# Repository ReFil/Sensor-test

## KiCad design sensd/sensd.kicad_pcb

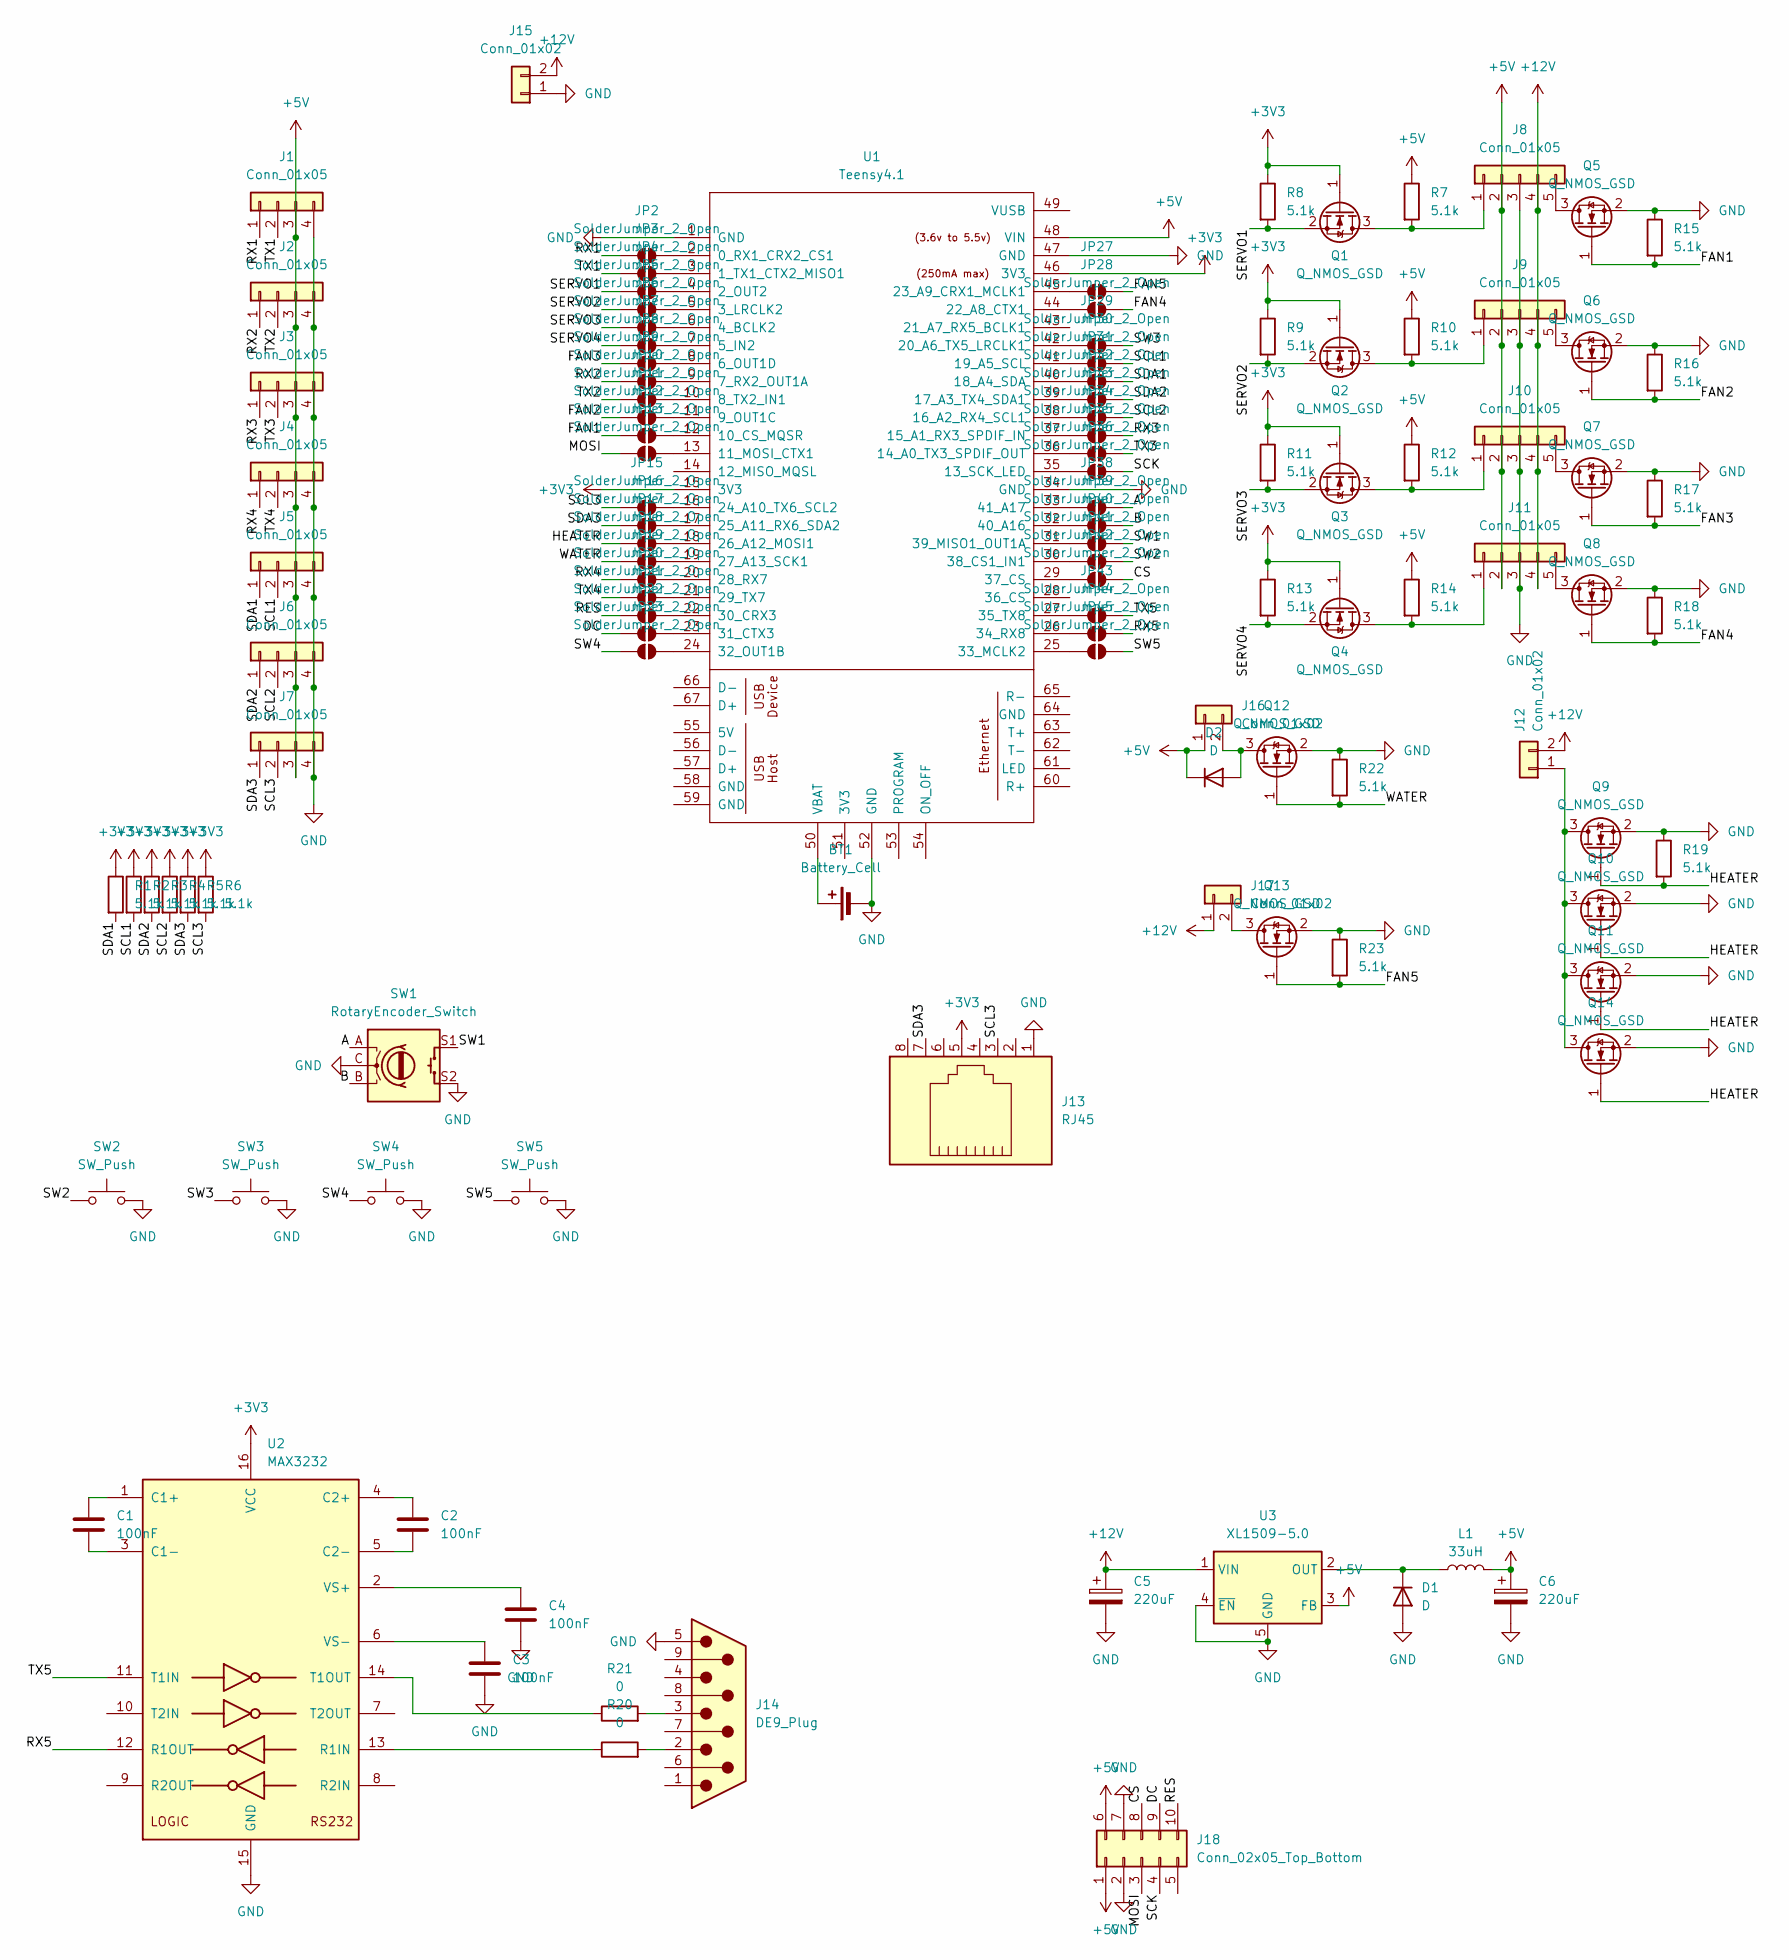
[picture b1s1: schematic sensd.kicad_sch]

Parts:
BT1: Battery_Cell; BatteryHolder_ComfortableElectronic_CH273-2450_1x2450
C1, C2, C3, C4: 100nF; C_0603_1608Metric; LCSC Part C1591
C5, C6: 220uF; CP_Elec_6.3x7.7; LCSC Part C2827940
D1, D2: D; D_SMA; LCSC Part C85098
J1, J2, J3, J4, J5, J6, J7: Conn_01x05; PinSocket_1x04_P2.54mm_Vertical
J8, J9, J10, J11: Conn_01x05; PinSocket_1x05_P2.54mm_Vertical
J12: Conn_01x02; AMASS_XT30PW-F_1x02_P2.50mm_Horizontal
J13: RJ45; RJ45_Amphenol_54602-x08_Horizontal
J14: DE9_Plug; DSUB-9_Female_Vertical_P2.77x2.84mm
J15: Conn_01x02; AMASS_XT60PW-M_1x02_P7.20mm_Horizontal
J16, J17: Conn_01x02; PinSocket_1x02_P2.54mm_Vertical
J18: Conn_02x05_Top_Bottom; PinHeader_2x05_P2.54mm_Vertical
JP2, JP3, JP4, JP5, JP6, JP7, JP8, JP9, JP10, JP11, JP12, JP13, JP15, JP16, JP17, JP18, JP19, JP20, JP21, JP22, JP23, JP27, JP28, JP29, JP30, JP31, JP32, JP33, JP34, JP35, JP36, JP38, JP39, JP40, JP41, JP42, JP43, JP44, JP45: SolderJumper_2_Open; SolderJumper-2_P1.3mm_Open_TrianglePad1.0x1.5mm
L1: 33uH; L_7.3x7.3_H3.5; LCSC Part C3002653
Q1, Q2, Q3, Q4, Q5, Q6, Q7, Q8, Q9, Q10, Q11, Q12, Q13, Q14: Q_NMOS_GSD; SOT-23; LCSC Part C414015
R1, R2, R3, R4, R5, R6, R7, R8, R9, R10, R11, R12, R13, R14, R15, R16, R17, R18, R19, R22, R23: 5.1k; R_0603_1608Metric; LCSC Part C26000
R20, R21: 0; R_0603_1608Metric
SW1: RotaryEncoder_Switch; RotaryEncoder_Bourns_Vertical_PEC12R-3x17F-Sxxxx
SW2, SW3, SW4, SW5: SW_Push; SW_Cherry_MX_1.00u_PCB
U1: Teensy4.1; Teensy41
U2: MAX3232; SOIC-16_3.9x9.9mm_P1.27mm; LCSC Part C45843
U3: XL1509-5.0; SOIC-8_3.9x4.9mm_P1.27mm; LCSC Part C2902368

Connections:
+3V3: J13.5, Q1.1 (G), Q2.1 (G), Q3.1 (G), Q4.1 (G), R1.1, R2.1, R3.1, R4.1, R5.1, R6.1, R8.1, R9.1, R11.1, R13.1, U1.15 (3V3), U1.46 (3V3), U2.16 (VCC)
+5V: C6.1, D2.1 (K), J1.3, J2.3, J3.3, J4.3, J5.3, J6.3, J7.3, J8.2, J9.2, J10.2, J11.2, J16.1, J18.1, J18.6, L1.2, R7.1, R10.1, R12.1, R14.1, U1.48 (VIN), U3.3 (FB)
+12V: C5.1, J8.4, J9.4, J10.4, J11.4, J12.2, J15.2, J17.1, U3.1 (VIN)
/A: JP38.2 (B), SW1.A
/B: JP39.2 (B), SW1.B
/CS: J18.8, JP42.2 (B)
/DC: J18.9, JP22.1 (A)
/FAN1: JP12.1 (A), Q5.1 (G), R15.2
/FAN2: JP11.1 (A), Q6.1 (G), R16.2
/FAN3: JP8.1 (A), Q7.1 (G), R17.2
/FAN4: JP28.2 (B), Q8.1 (G), R18.2
/FAN5: JP27.2 (B), Q13.1 (G), R23.2
/HEATER: JP17.1 (A), Q9.1 (G), Q10.1 (G), Q11.1 (G), Q14.1 (G), R19.2
/MOSI: J18.3, JP13.1 (A)
/RES: J18.10, JP21.1 (A)
/RX1: J1.1, JP2.1 (A)
/RX2: J2.1, JP9.1 (A)
/RX3: J3.1, JP34.2 (B)
/RX4: J4.1, JP19.1 (A)
/RX5: JP44.2 (B), U2.12 (R1OUT)
/SCK: J18.4, JP36.2 (B)
/SCL1: J5.2, JP30.2 (B), R2.2
/SCL2: J6.2, JP33.2 (B), R4.2
/SCL3: J7.2, J13.3, JP15.1 (A), R6.2
/SDA1: J5.1, JP31.2 (B), R1.2
/SDA2: J6.1, JP32.2 (B), R3.2
/SDA3: J7.1, J13.7, JP16.1 (A), R5.2
/SERVO1: JP4.1 (A), Q1.2 (S), R8.2
/SERVO2: JP5.1 (A), Q2.2 (S), R9.2
/SERVO3: JP6.1 (A), Q3.2 (S), R11.2
/SERVO4: JP7.1 (A), Q4.2 (S), R13.2
/SW1: JP40.2 (B), SW1.S1
/SW2: JP41.2 (B), SW2.1
/SW3: JP29.2 (B), SW3.1
/SW4: JP23.1 (A), SW4.1
/SW5: JP45.2 (B), SW5.1
/TX1: J1.2, JP3.1 (A)
/TX2: J2.2, JP10.1 (A)
/TX3: J3.2, JP35.2 (B)
/TX4: J4.2, JP20.1 (A)
/TX5: JP43.2 (B), U2.11 (T1IN)
/WATER: JP18.1 (A), Q12.1 (G), R22.2
GND: BT1.2 (-), C3.2, C4.2, C5.2, C6.2, D1.2 (A), J1.4, J2.4, J3.4, J4.4, J5.4, J6.4, J7.4, J8.3, J9.3, J10.3, J11.3, J13.1, J14.5, J15.1, J18.2, J18.7, Q5.2 (S), Q6.2 (S), Q7.2 (S), Q8.2 (S), Q9.2 (S), Q10.2 (S), Q11.2 (S), Q12.2 (S), Q13.2 (S), Q14.2 (S), R15.1, R16.1, R17.1, R18.1, R19.1, R22.1, R23.1, SW1.C, SW1.S2, SW2.2, SW3.2, SW4.2, SW5.2, U1.1 (GND), U1.34 (GND), U1.47 (GND), U1.52 (GND), U2.15 (GND), U3.4 (~EN), U3.5 (GND), U3.6 (GND), U3.7 (GND), U3.8 (GND)
unnamed: BT1.1 (+), U1.50 (VBAT)
unnamed: D1.1 (K), L1.1, U3.2 (OUT)
unnamed: D2.2 (A), J16.2, Q12.3 (D)
unnamed: J8.1, Q1.3 (D), R7.2
unnamed: J8.5, Q5.3 (D)
unnamed: J9.1, Q2.3 (D), R10.2
unnamed: J9.5, Q6.3 (D)
unnamed: J10.1, Q3.3 (D), R12.2
unnamed: J10.5, Q7.3 (D)
unnamed: J11.1, Q4.3 (D), R14.2
unnamed: J11.5, Q8.3 (D)
unnamed: J12.1, Q9.3 (D), Q10.3 (D), Q11.3 (D), Q14.3 (D)
unnamed: J14.2, R20.2
unnamed: J14.3, R21.2
unnamed: J17.2, Q13.3 (D)
unnamed: JP2.2 (B), U1.2 (0_RX1_CRX2_CS1)
unnamed: JP3.2 (B), U1.3 (1_TX1_CTX2_MISO1)
unnamed: JP4.2 (B), U1.4 (2_OUT2)
unnamed: JP5.2 (B), U1.5 (3_LRCLK2)
unnamed: JP6.2 (B), U1.6 (4_BCLK2)
unnamed: JP7.2 (B), U1.7 (5_IN2)
unnamed: JP8.2 (B), U1.8 (6_OUT1D)
unnamed: JP9.2 (B), U1.9 (7_RX2_OUT1A)
unnamed: JP10.2 (B), U1.10 (8_TX2_IN1)
unnamed: JP11.2 (B), U1.11 (9_OUT1C)
unnamed: JP12.2 (B), U1.12 (10_CS_MQSR)
unnamed: JP13.2 (B), U1.13 (11_MOSI_CTX1)
unnamed: JP15.2 (B), U1.16 (24_A10_TX6_SCL2)
unnamed: JP16.2 (B), U1.17 (25_A11_RX6_SDA2)
unnamed: JP17.2 (B), U1.18 (26_A12_MOSI1)
unnamed: JP18.2 (B), U1.19 (27_A13_SCK1)
unnamed: JP19.2 (B), U1.20 (28_RX7)
unnamed: JP20.2 (B), U1.21 (29_TX7)
unnamed: JP21.2 (B), U1.22 (30_CRX3)
unnamed: JP22.2 (B), U1.23 (31_CTX3)
unnamed: JP23.2 (B), U1.24 (32_OUT1B)
unnamed: JP27.1 (A), U1.45 (23_A9_CRX1_MCLK1)
unnamed: JP28.1 (A), U1.44 (22_A8_CTX1)
unnamed: JP29.1 (A), U1.42 (20_A6_TX5_LRCLK1)
unnamed: JP30.1 (A), U1.41 (19_A5_SCL)
unnamed: JP31.1 (A), U1.40 (18_A4_SDA)
unnamed: JP32.1 (A), U1.39 (17_A3_TX4_SDA1)
unnamed: JP33.1 (A), U1.38 (16_A2_RX4_SCL1)
unnamed: JP34.1 (A), U1.37 (15_A1_RX3_SPDIF_IN)
unnamed: JP35.1 (A), U1.36 (14_A0_TX3_SPDIF_OUT)
unnamed: JP36.1 (A), U1.35 (13_SCK_LED)
unnamed: JP38.1 (A), U1.33 (41_A17)
unnamed: JP39.1 (A), U1.32 (40_A16)
unnamed: JP40.1 (A), U1.31 (39_MISO1_OUT1A)
unnamed: JP41.1 (A), U1.30 (38_CS1_IN1)
unnamed: JP42.1 (A), U1.29 (37_CS)
unnamed: JP43.1 (A), U1.27 (35_TX8)
unnamed: JP44.1 (A), U1.26 (34_RX8)
unnamed: JP45.1 (A), U1.25 (33_MCLK2)
unnamed: C1.1, U2.1 (C1+)
unnamed: C1.2, U2.3 (C1-)
unnamed: C2.1, U2.4 (C2+)
unnamed: C2.2, U2.5 (C2-)
unnamed: R20.1, U2.13 (R1IN)
unnamed: R21.1, U2.14 (T1OUT)
unnamed: C4.1, U2.2 (VS+)
unnamed: C3.1, U2.6 (VS-)

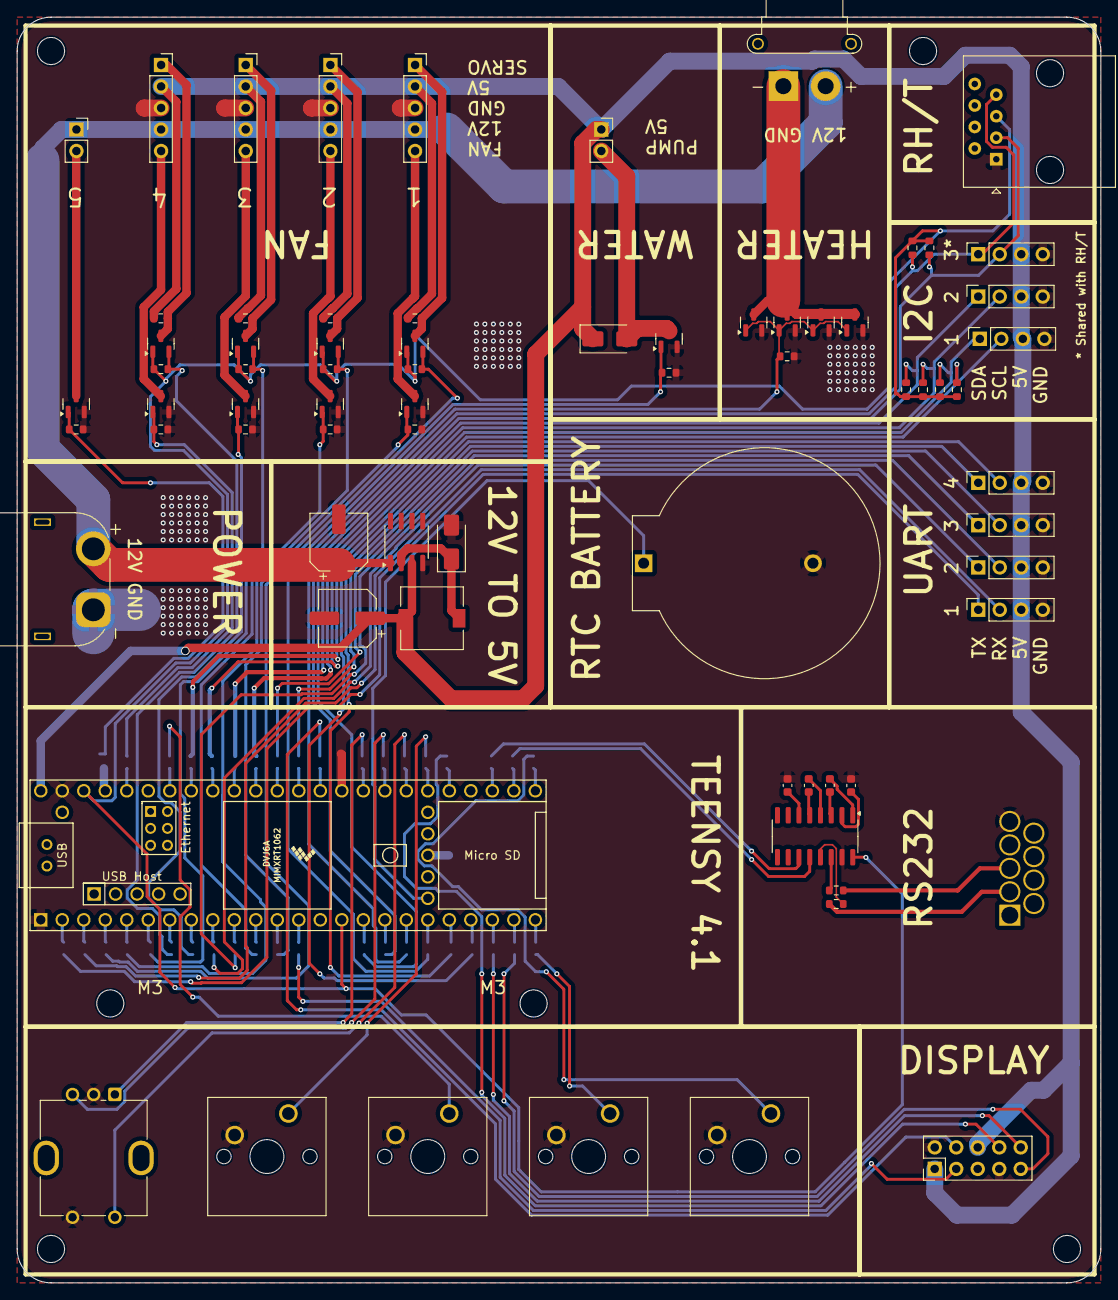
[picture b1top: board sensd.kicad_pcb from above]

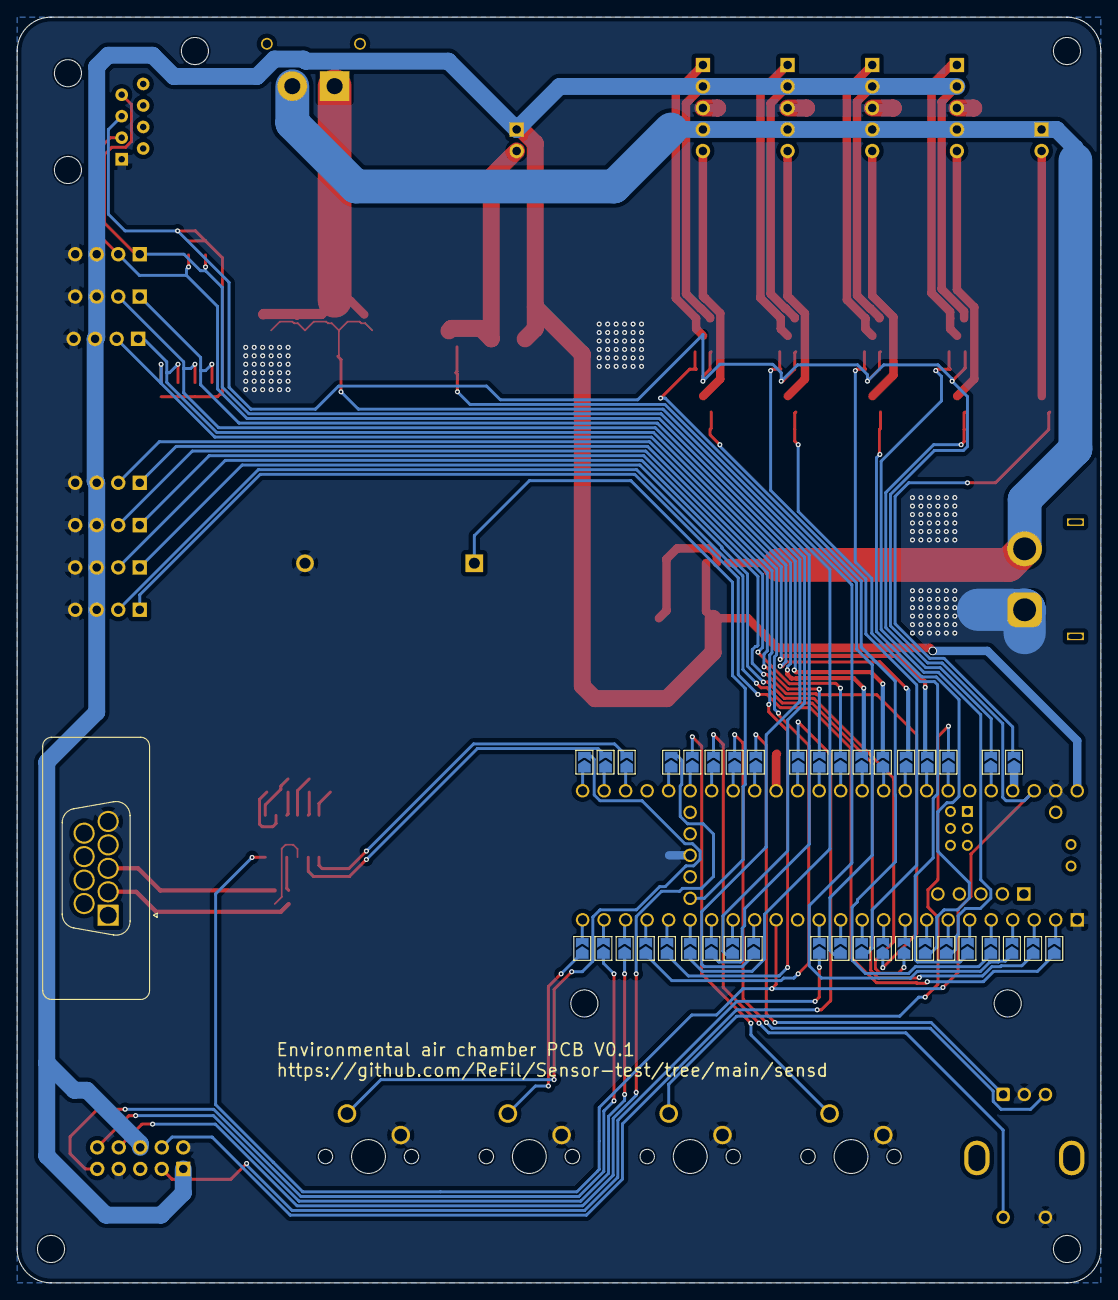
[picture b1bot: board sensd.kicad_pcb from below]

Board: 2 copper layers, 128.0 x 149.5 mm, 112 parts (40 on the bottom side), 105 nets.

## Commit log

2023-03-03 In progress
2023-03-29 Adding lots of data
2023-06-12 Lotsa updates
2023-07-28 meauring rht
2023-08-17 dsfjkhsdfhjkadsfkjh
2023-09-25 New data changes
2024-01-12 new dataa
2024-01-17 more data
2024-03-26 Testingstuff
2024-06-10 New PCB
2024-06-10 Nearly done with sch
2024-06-12 board completed
2024-07-11 I can tell this is gonna break me
2026-01-11 Sensor test changes
